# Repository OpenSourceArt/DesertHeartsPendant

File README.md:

A 3D printed Desert Hearts pendant with color fading LEDs. Circuit board created using EaglePCB. Consists of two parts, the main housing, and a transparent faceplate.

3D models:

Printed parts. Housing was created using Shapeways "Black Strong & Flexible" plastic. Faceplate is Shapeways "Frosted Ultra Detail" plastic.

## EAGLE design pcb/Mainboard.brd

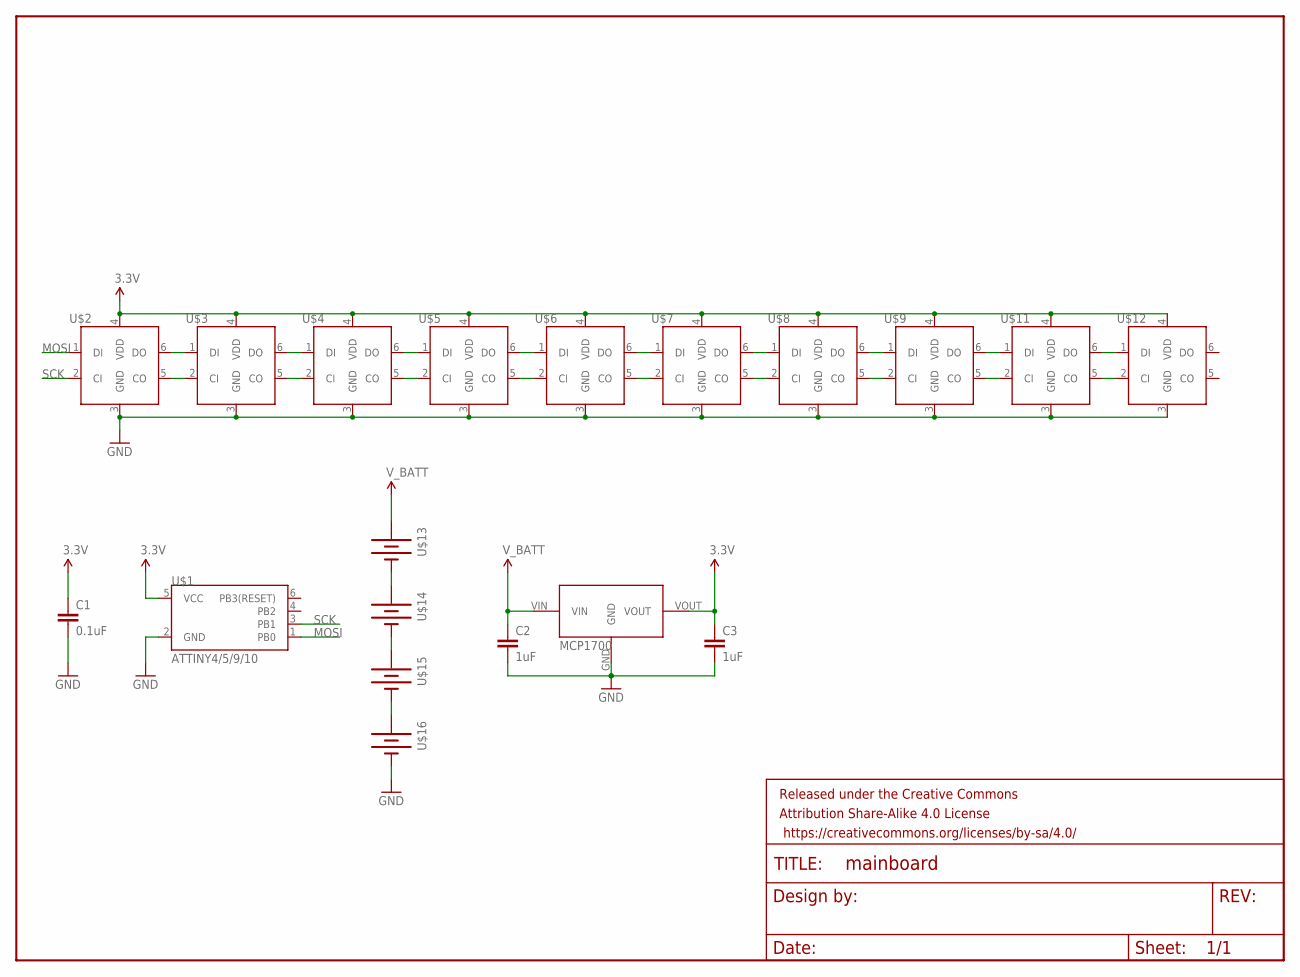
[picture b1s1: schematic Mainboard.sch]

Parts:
C1: 0.1uF; 0402-CAP
C2, C3: 1uF; 0402-CAP
FRAME1: FRAME-LETTER; CREATIVE_COMMONS
U$1: ATTINY4/5/9/10; SOT23-6
U$2, U$3, U$4, U$5, U$6, U$7, U$8, U$9, U$11, U$12: APA102C; LED-TRICOLOR-5050-IC
U$13, U$14, U$15, U$16: AAAA-BATTERYS; KEYSTONE-SMD-AAAA-CLIPS
U$17: MCP1700

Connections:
3.3V: C1.1, C3.1, U$1.5 (VCC), U$2.4 (VDD), U$3.4 (VDD), U$4.4 (VDD), U$5.4 (VDD), U$6.4 (VDD), U$7.4 (VDD), U$8.4 (VDD), U$9.4 (VDD), U$11.4 (VDD), U$12.4 (VDD), U$17.VOUT
GND: C1.2, C2.2, C3.2, U$1.2 (GND), U$2.3 (GND), U$3.3 (GND), U$4.3 (GND), U$5.3 (GND), U$6.3 (GND), U$7.3 (GND), U$8.3 (GND), U$9.3 (GND), U$11.3 (GND), U$12.3 (GND), U$16.P$2 (-), U$17.GND
MOSI: U$1.1 (PB0), U$2.1 (DI)
unnamed: U$2.6 (DO), U$3.1 (DI)
unnamed: U$2.5 (CO), U$3.2 (CI)
unnamed: U$3.5 (CO), U$4.2 (CI)
unnamed: U$4.5 (CO), U$5.2 (CI)
unnamed: U$5.5 (CO), U$6.2 (CI)
unnamed: U$13.P$2 (-), U$14.P$1 (+)
unnamed: U$6.5 (CO), U$7.2 (CI)
unnamed: U$6.6 (DO), U$7.1 (DI)
unnamed: U$5.6 (DO), U$6.1 (DI)
unnamed: U$4.6 (DO), U$5.1 (DI)
unnamed: U$3.6 (DO), U$4.1 (DI)
unnamed: U$7.6 (DO), U$8.1 (DI)
unnamed: U$7.5 (CO), U$8.2 (CI)
unnamed: U$8.6 (DO), U$9.1 (DI)
unnamed: U$8.5 (CO), U$9.2 (CI)
unnamed: U$9.6 (DO), U$11.1 (DI)
unnamed: U$9.5 (CO), U$11.2 (CI)
unnamed: U$11.6 (DO), U$12.1 (DI)
unnamed: U$11.5 (CO), U$12.2 (CI)
unnamed: U$14.P$2 (-), U$15.P$1 (+)
unnamed: U$15.P$2 (-), U$16.P$1 (+)
SCK: U$1.3 (PB1), U$2.2 (CI)
V_BATT: C2.1, U$13.P$1 (+), U$17.VIN

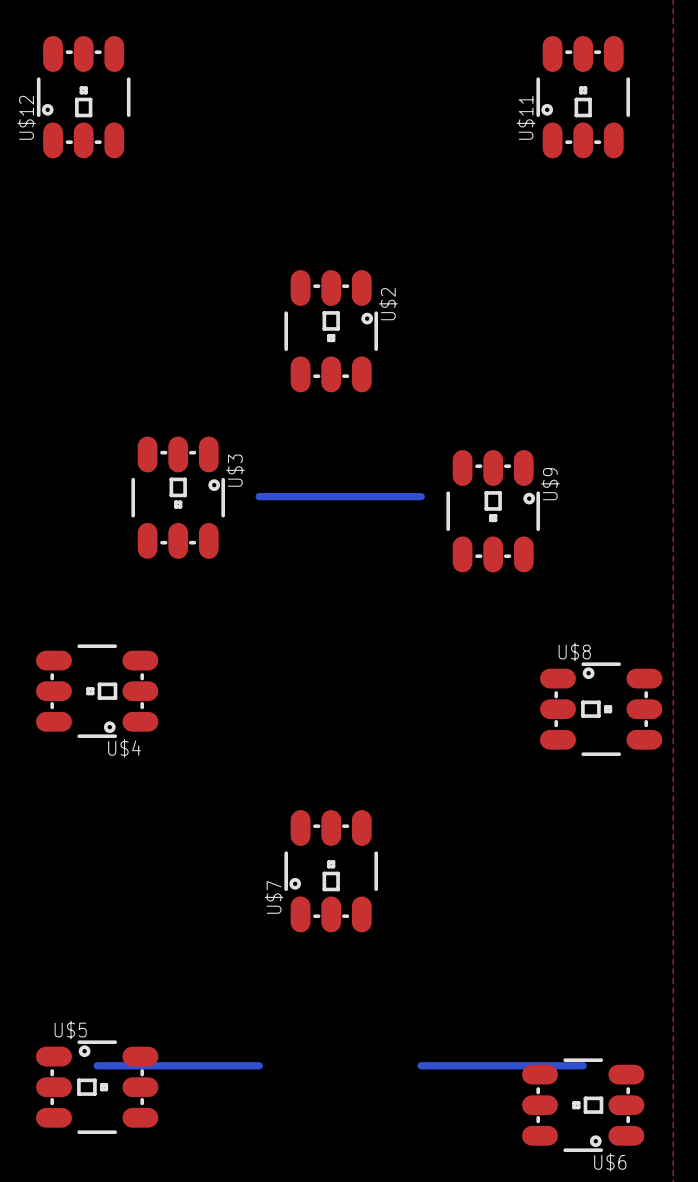
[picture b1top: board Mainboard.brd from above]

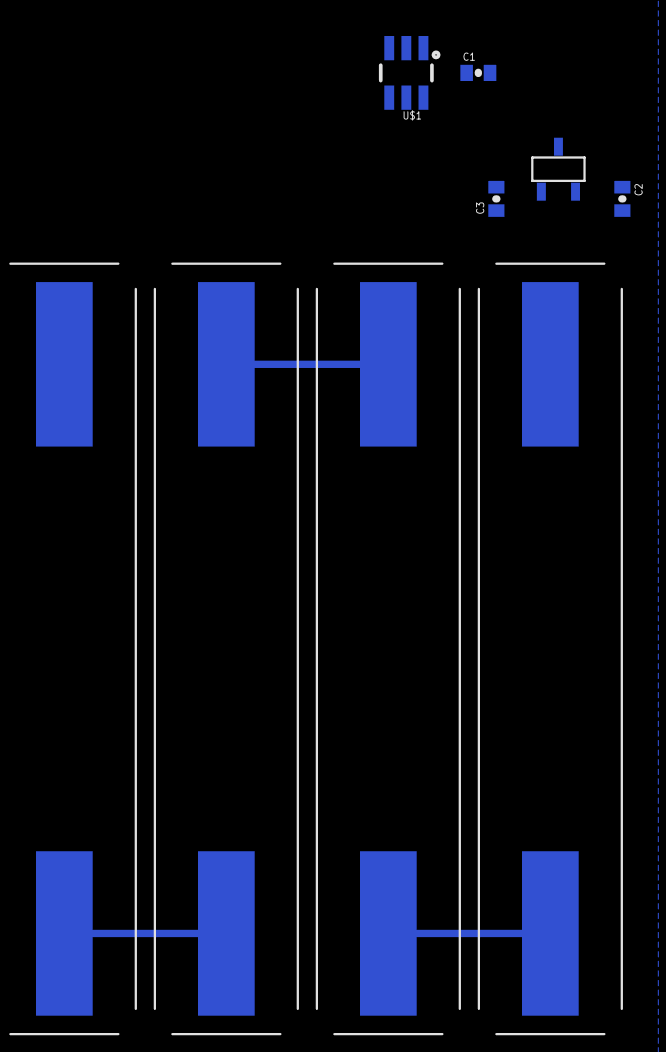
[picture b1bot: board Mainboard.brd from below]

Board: 2 copper layers, 20 parts (9 on the bottom side), 26 nets.

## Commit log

2016-01-03 Initial commit. Through-hole coin cell version.
2016-01-06 Started SMD redesign.

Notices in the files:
parts and their libraries:
SparkFun-Aesthetics: Licensing: Creative Commons ShareAlike 4.0 International - https://creativecommons.org/licenses/by-sa/4.0
SparkFun-Aesthetics: Released under the Creative Commons Attribution Share-Alike 4.0 License
SparkFun-Aesthetics: https://creativecommons.org/licenses/by-sa/4.0
